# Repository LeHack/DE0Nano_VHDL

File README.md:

# DE0 Nano VHDL examples

This repository contains simple examples showing how to manipulate different devices in VHDL from a DE0 Nano FPGA board.

* [Simple example of using a MAX7219 based LED Matrix via the SPI protocol.](src/LEDMatrix)
* [Read data from a DE0 Nano ADC and display it on a MAX7219 LED Matrix (both using the SPI protocol).](src/ADC_LEDMatrix)
* [Controlling a 4 digit 8 segment display (FJ-5461BH) with the use of 7 pins.](src/SegmentDisplay)
* more to come...

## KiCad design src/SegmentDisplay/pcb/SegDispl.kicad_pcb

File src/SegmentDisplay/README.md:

# 4 digit 8 segment display (FJ-5461BH) example usage in VHDL

Simple proof of concept on how to manipulate a 4 digit display (7 segment + DP) using a FPGA (7 pins), a 8-bit SIPO register and two 3-channel multiplexers.

### Notes:

Example pin assignments for DE0 Nano:
* CLOCK 50: R8

Register (74HC595):
* CLK: R13 (SHCP/SRCLK)
* LATCH: T11 (STCP/RCLK)
* DATA: R12 (DS/SER)

Multiplexers (74HC4053):
* MLTPLX_CH 0: T10 (#1 S1/D1S)
* MLTPLX_CH 1: R11 (#1 S2/D2S)
* MLTPLX_CH 2: P11 (#2 S1/D3S)
* MLTPLX_CH 3: R10 (#2 S2/D4S)

Below is a circuit and pcb design that can be used with this example:  

Example pin mapping for the above circuit and a DE0 Nano (GPIO-1):
* PIN 1: GND
* PIN 2: GPIO_17
* PIN 3: GPIO_14
* PIN 4: GPIO_16
* PIN 5: GPIO_111
* PIN 6: GPIO_110
* PIN 7: GPIO_109
* PIN 8: GPIO_108
* PIN 9: VCC

In order to run a simulation, set the Library (in project files properties) to "utils" for all files added from within the "utils" subdirectory.

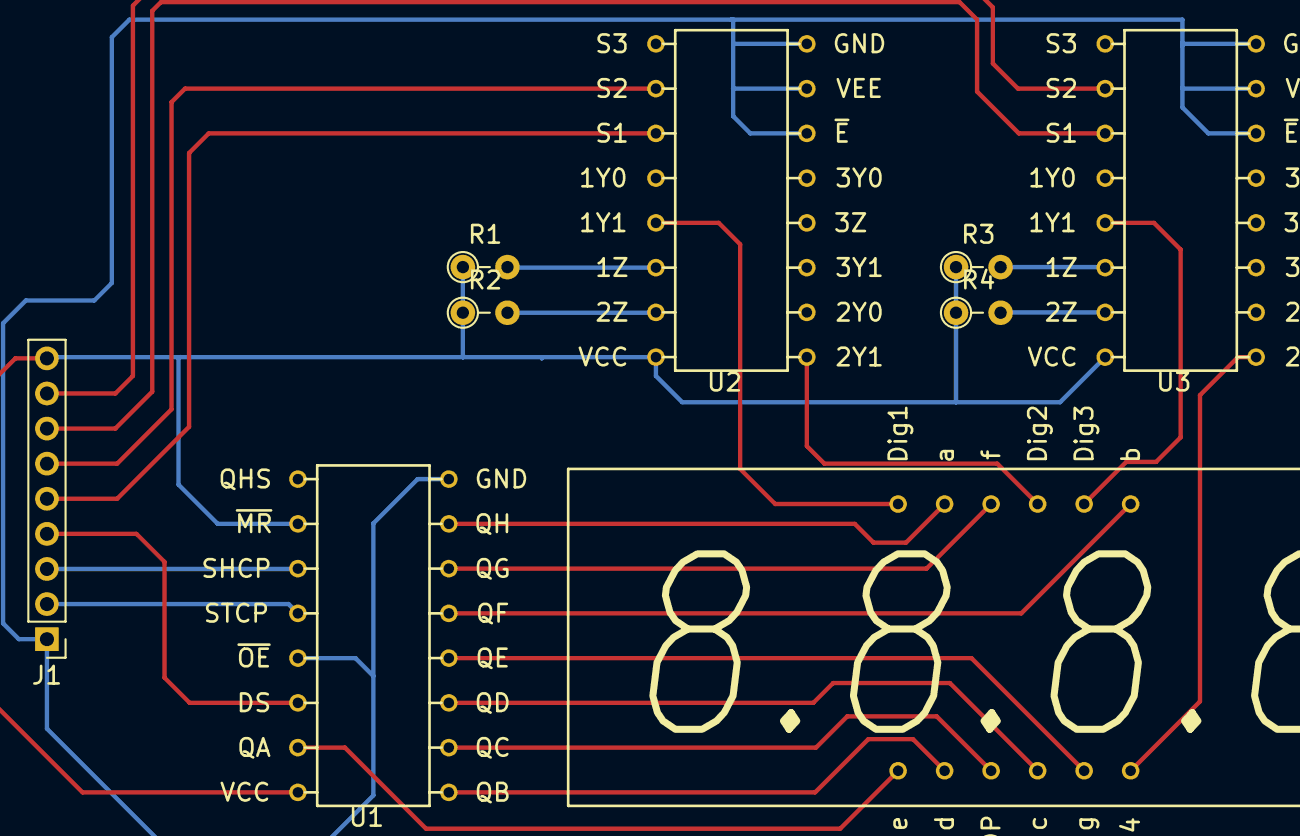
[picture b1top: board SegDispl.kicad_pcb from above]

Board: 2 copper layers, 9 parts (0 on the bottom side), 25 nets.

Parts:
J1: CONN_01X09; Pin_Header_Straight_1x09_Pitch2.00mm
R1, R2, R3, R4: 650; R_Axial_DIN0204_L3.6mm_D1.6mm_P2.54mm_Vertical
U1: 74HC595-2; 74HC595
U2, U3: 74HC4053
U4: FJ-5461BH

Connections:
/D1S: J1.5, U2.11
/D2S: J1.6, U2.10
/D3S: J1.7, U3.11
/D4S: J1.8, U3.10
/Dig1: U2.13, U4.12
/Dig2: U2.1, U4.9
/Dig3: U3.13, U4.8
/Dig4: U3.1, U4.6
/GND: J1.1, U1.8, U1.13, U2.6, U2.7, U2.8, U3.6, U3.7, U3.8
/VDD: J1.9, R1.1, R2.1, R3.1, R4.1, U1.10, U1.16, U2.16, U3.16
unnamed: J1.2, U1.12
unnamed: J1.3, U1.11
unnamed: J1.4, U1.14
unnamed: R1.2, U2.14
unnamed: R2.2, U2.15
unnamed: R3.2, U3.14
unnamed: R4.2, U3.15
unnamed: U1.1, U4.2
unnamed: U1.2, U4.3
unnamed: U1.3, U4.4
unnamed: U1.4, U4.5
unnamed: U1.5, U4.7
unnamed: U1.6, U4.10
unnamed: U1.7, U4.11
unnamed: U1.15, U4.1

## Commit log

2016-10-25 A very rough example, will be cleaned up soon.
2016-10-26 Some improvements (removed duplicate component declaration).
2016-10-26 Split initialization from operation.
2016-10-26 Moved setup/control logic to led_matrix.vhd
2016-10-26 Fix animation, convert tabs to 4 spaces.
2016-10-26 Improve setup procedure, remove debug, optimize clock divide fastest to error free setting.
2016-10-26 Moved animation driver to main entity. One more issue to resolve regarding the last line of the matrix display (most possibly some off-by-1 error).
2016-10-27 Brain dump
2016-11-01 Fixed animation issue (last row refreshed on next iteration). Also added virt_clk to lock out SPI transfer-time clk events.
2016-11-01 Small fix regarding logic.
2016-11-02 Reduced number of unused cycles.
2016-11-04 Expanded previous example to control two displays at once using the simplest possible approach.
2016-11-04 Simple digit display (<=99)
2017-06-21 Reworked the LEDMatrix example.
2017-06-21 Split architecture and entities into separate files.
2017-06-21 Fix link in main readme
2017-06-21 Added example of how to use the DE0Nano integrated ADC.
2017-06-21 Update licence
2017-06-21 Reduced the required delay before passing SPI-read results to minimum.
2017-07-05 Added a demo of a 4 digit 8 segment display.
2017-07-05 Updated circuit image.
2017-07-07 Updated refences to match diagram.
2017-07-11 Added DE0Nano pin mapping for the circuit.
2017-07-11 Fixed pin mapping order for digits.
